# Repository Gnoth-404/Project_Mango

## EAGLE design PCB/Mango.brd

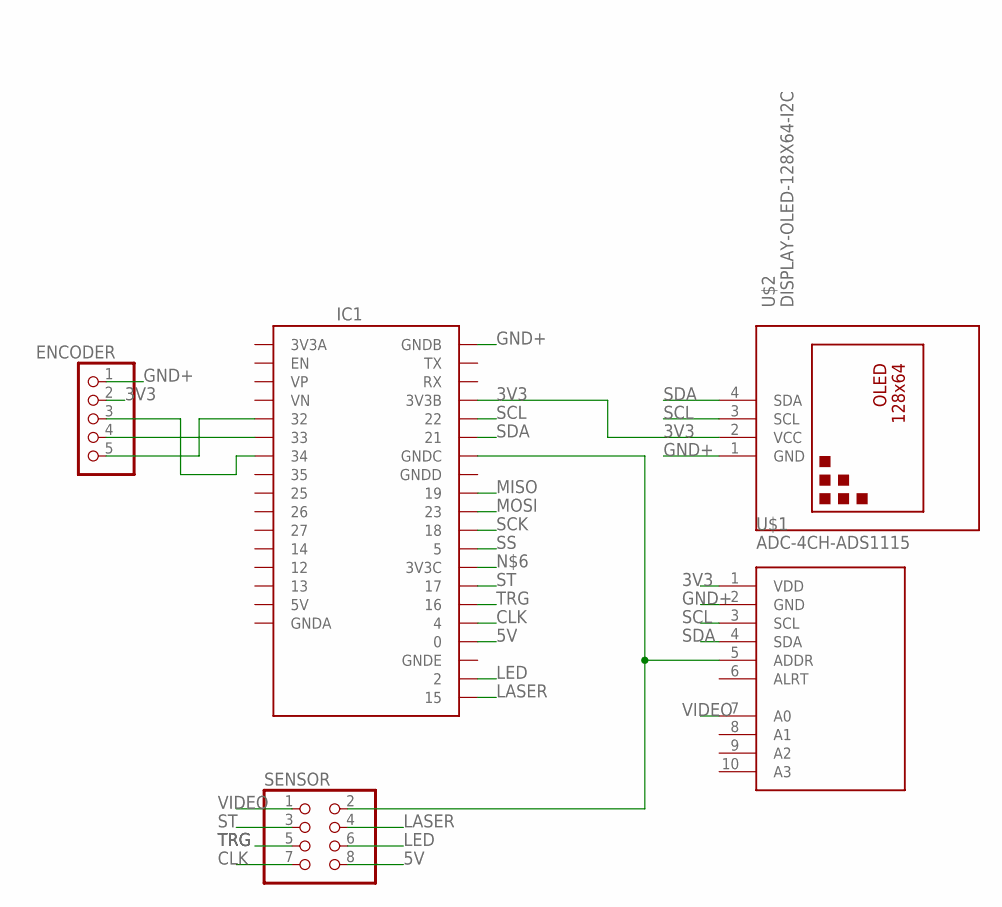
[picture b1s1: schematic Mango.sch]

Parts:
ENCODER: PINHD-1X5; 1X05
IC1: SSFD_LOLIN32_WEMOS_CHINA_W_BATT
SENSOR: PINHD-2X4; 2X04
U$1: ADC-4CH-ADS1115
U$2: DISPLAY-OLED-128X64-I2C

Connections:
3V3: ENCODER.2, IC1.3V3B, U$1.1 (VDD), U$2.2 (VCC)
5V: IC1.0, SENSOR.8
CLK: IC1.4, SENSOR.7
GND+: ENCODER.1, IC1.GNDB, U$1.2 (GND), U$2.1 (GND)
LASER: IC1.15, SENSOR.4
LED: IC1.2, SENSOR.6
MISO: IC1.19
MOSI: IC1.23
unnamed: ENCODER.5, IC1.32
unnamed: ENCODER.3, IC1.34
unnamed: ENCODER.4, IC1.33
unnamed: IC1.GNDC, SENSOR.2, U$1.5 (ADDR)
SCK: IC1.18
SCL: IC1.22, U$1.3 (SCL), U$2.3 (SCL)
SDA: IC1.21, U$1.4 (SDA), U$2.4 (SDA)
SS: IC1.5
ST: IC1.17, SENSOR.3
TRG: IC1.16, SENSOR.5
VIDEO: SENSOR.1, U$1.7 (A0)

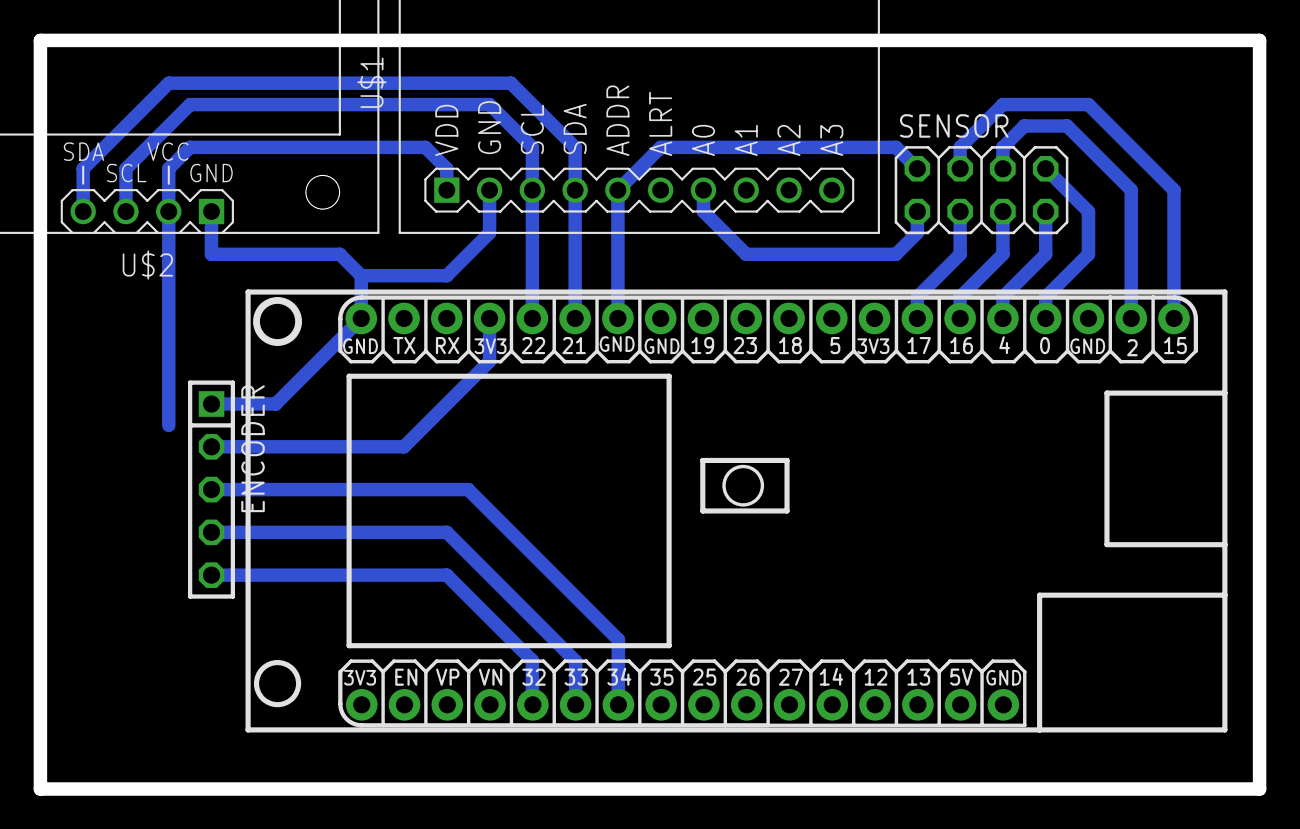
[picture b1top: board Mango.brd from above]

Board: 2 copper layers, 72.4 x 44.5 mm, 5 parts (0 on the bottom side), 15 nets.

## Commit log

2020-09-23 Adding file
2020-09-23 Add resource file+ folder
2020-09-23 hello
2020-10-06 Create Example_Setup
    How to use spectrometer
2020-10-08 change
2020-10-11 Change file+ auto reconnect
2020-10-11 hihi
2020-10-11 no more engrisk
2020-10-19 Change location
2020-10-20 Change sensor config
    More stable, connect to heroku web server
2020-10-20 Get data from firebase --> excel
2020-10-20 Clean shit code
2020-11-03 Added Untitled Diagram.drawio
2022-03-21 Initial Commit
    Project mango update

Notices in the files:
parts and their libraries:
diy-modules: Released under the Creative Commons Attribution 4.0 International License: http://creativecommons.org/licenses/by/4.0
